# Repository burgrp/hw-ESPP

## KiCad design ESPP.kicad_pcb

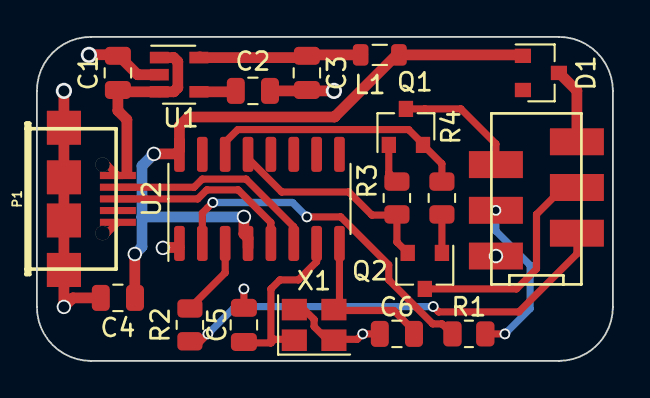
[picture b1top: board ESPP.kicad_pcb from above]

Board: 2 copper layers, 32.0 x 18.0 mm, 19 parts (0 on the bottom side), 20 nets.

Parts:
C1, C3: 1u; C_0805_2012Metric
C2: 22n; C_0805_2012Metric
C4: 100n; C_0805_2012Metric
C5, C6: 22p; C_0805_2012Metric
D1: BAT54C; SOT-23
L1: Ferrite bead; L_0805_2012Metric
P1: USB_OTG; conn_usb_B_micro_smd-2
Q1, Q2: MMBT3904; SOT-23
R1, R2: 1k5; R_0805_2012Metric
R3, R4: 10k; R_0805_2012Metric
U1: RT9193; SOT-23-5
U2: CH340G; SOIC-16_3.9x9.9mm_P1.27mm
X1: 12MHz; Crystal_SMD_3225-4Pin_3.2x2.5mm
X2: ESP-PROG; Micro-Match-FOB-6

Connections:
/5V-USB: C1.1, P1.1, U1.1, U1.3
/D+: P1.3, U2.5
/D-: P1.2, U2.6
/DTR: Q2.2, R3.1, U2.13
/GPIO0: Q2.3, X2.4
/RESET: Q1.3, X2.5
/RTS: Q1.2, R4.2, U2.14
/RX: R1.1, X2.3
/TX: R2.1, X2.2
GND: C1.2, C2.2, C3.2, C4.2, C5.2, C6.2, P1.5, P1.6, U1.2, U2.1, X1.2, X1.4, X2.1
unnamed: C2.1, U1.4
unnamed: C3.1, L1.2, U1.5
unnamed: C5.1, U2.7, X1.1
unnamed: C6.1, U2.8, X1.3
unnamed: D1.3, X2.6
unnamed: Q1.1, R3.2
unnamed: Q2.1, R4.1
unnamed: R1.2, U2.2
unnamed: R2.2, U2.3
VCC: C4.1, D1.1, L1.1, U2.4, U2.16

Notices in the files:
ESPP.kicad_pcb:
CC-BY-SA
